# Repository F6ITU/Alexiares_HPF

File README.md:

# Alexiares_HPF
This repository contains the High Pass Filter project of the OpenHPSDR Alexiares frontend

This work is protected by the TAPR Open Hardware Licence https://www.tapr.org/ohl.html

Original work by Graham Haddock, KE9H and Phil Harman, VK6APH.

for more informations, please refer to 

https://wiki.electrolab.fr/Projets:Lab:2017:Peripheriques_Angelia

3D image of the board are stored on this repo

HPF_top.jpg

HPF_bottom.jpg

Bom is available in CSV format

A separate BOM in XLS format is dedicated to filter capacitors

Note that ALL filter caps must be C0G or at least NP0 quality

Schematics, pcb design, modules and libs are in Kicad format

Gerber files are fully compatible with Protel 4.6 format

Board's dimensions are oversized to fit the 5x10 and 10x10cm size of all board of the Hermes project under Kicad:

* Alexandrie (Ἀλεξάνδρεια), Alexiares SPI interface
* Alexi2C ( Ἄλεξις), Alternate Alexiares I2C interface
* Alexiares_lpf (Ἀλεξιάρης) Alexiares low pass filter
* Alexiares_hpf (Ἀλεξιάρης) Alexiares high-pass filter
* Alexiares_Coax_Out (Ἀλεξιάρης ) Alexiares antenna switch boards
* Télémaque (Τηλέμαχος),  SSPA U/V/C°/Refl/FWD sensor for the Mentor board 
* Mentor (Μέντωρ) Micro-controler unit(MCU) and security module controling Telemaque informations
* Ulysse ou Odysseus (Ὀδυσσεύς), medium power reflectometer for the Telemaque/Mentor set
* Themis (Θέμις), low power bidirectionnal reflectometer with pre-distorsion (pure signal) output
* Aiôn (αἰών), 10 MHz low drift, low phase noise clock (general purpose)
* Hébé (Ἥβη), EER control system for high efficiency power amp

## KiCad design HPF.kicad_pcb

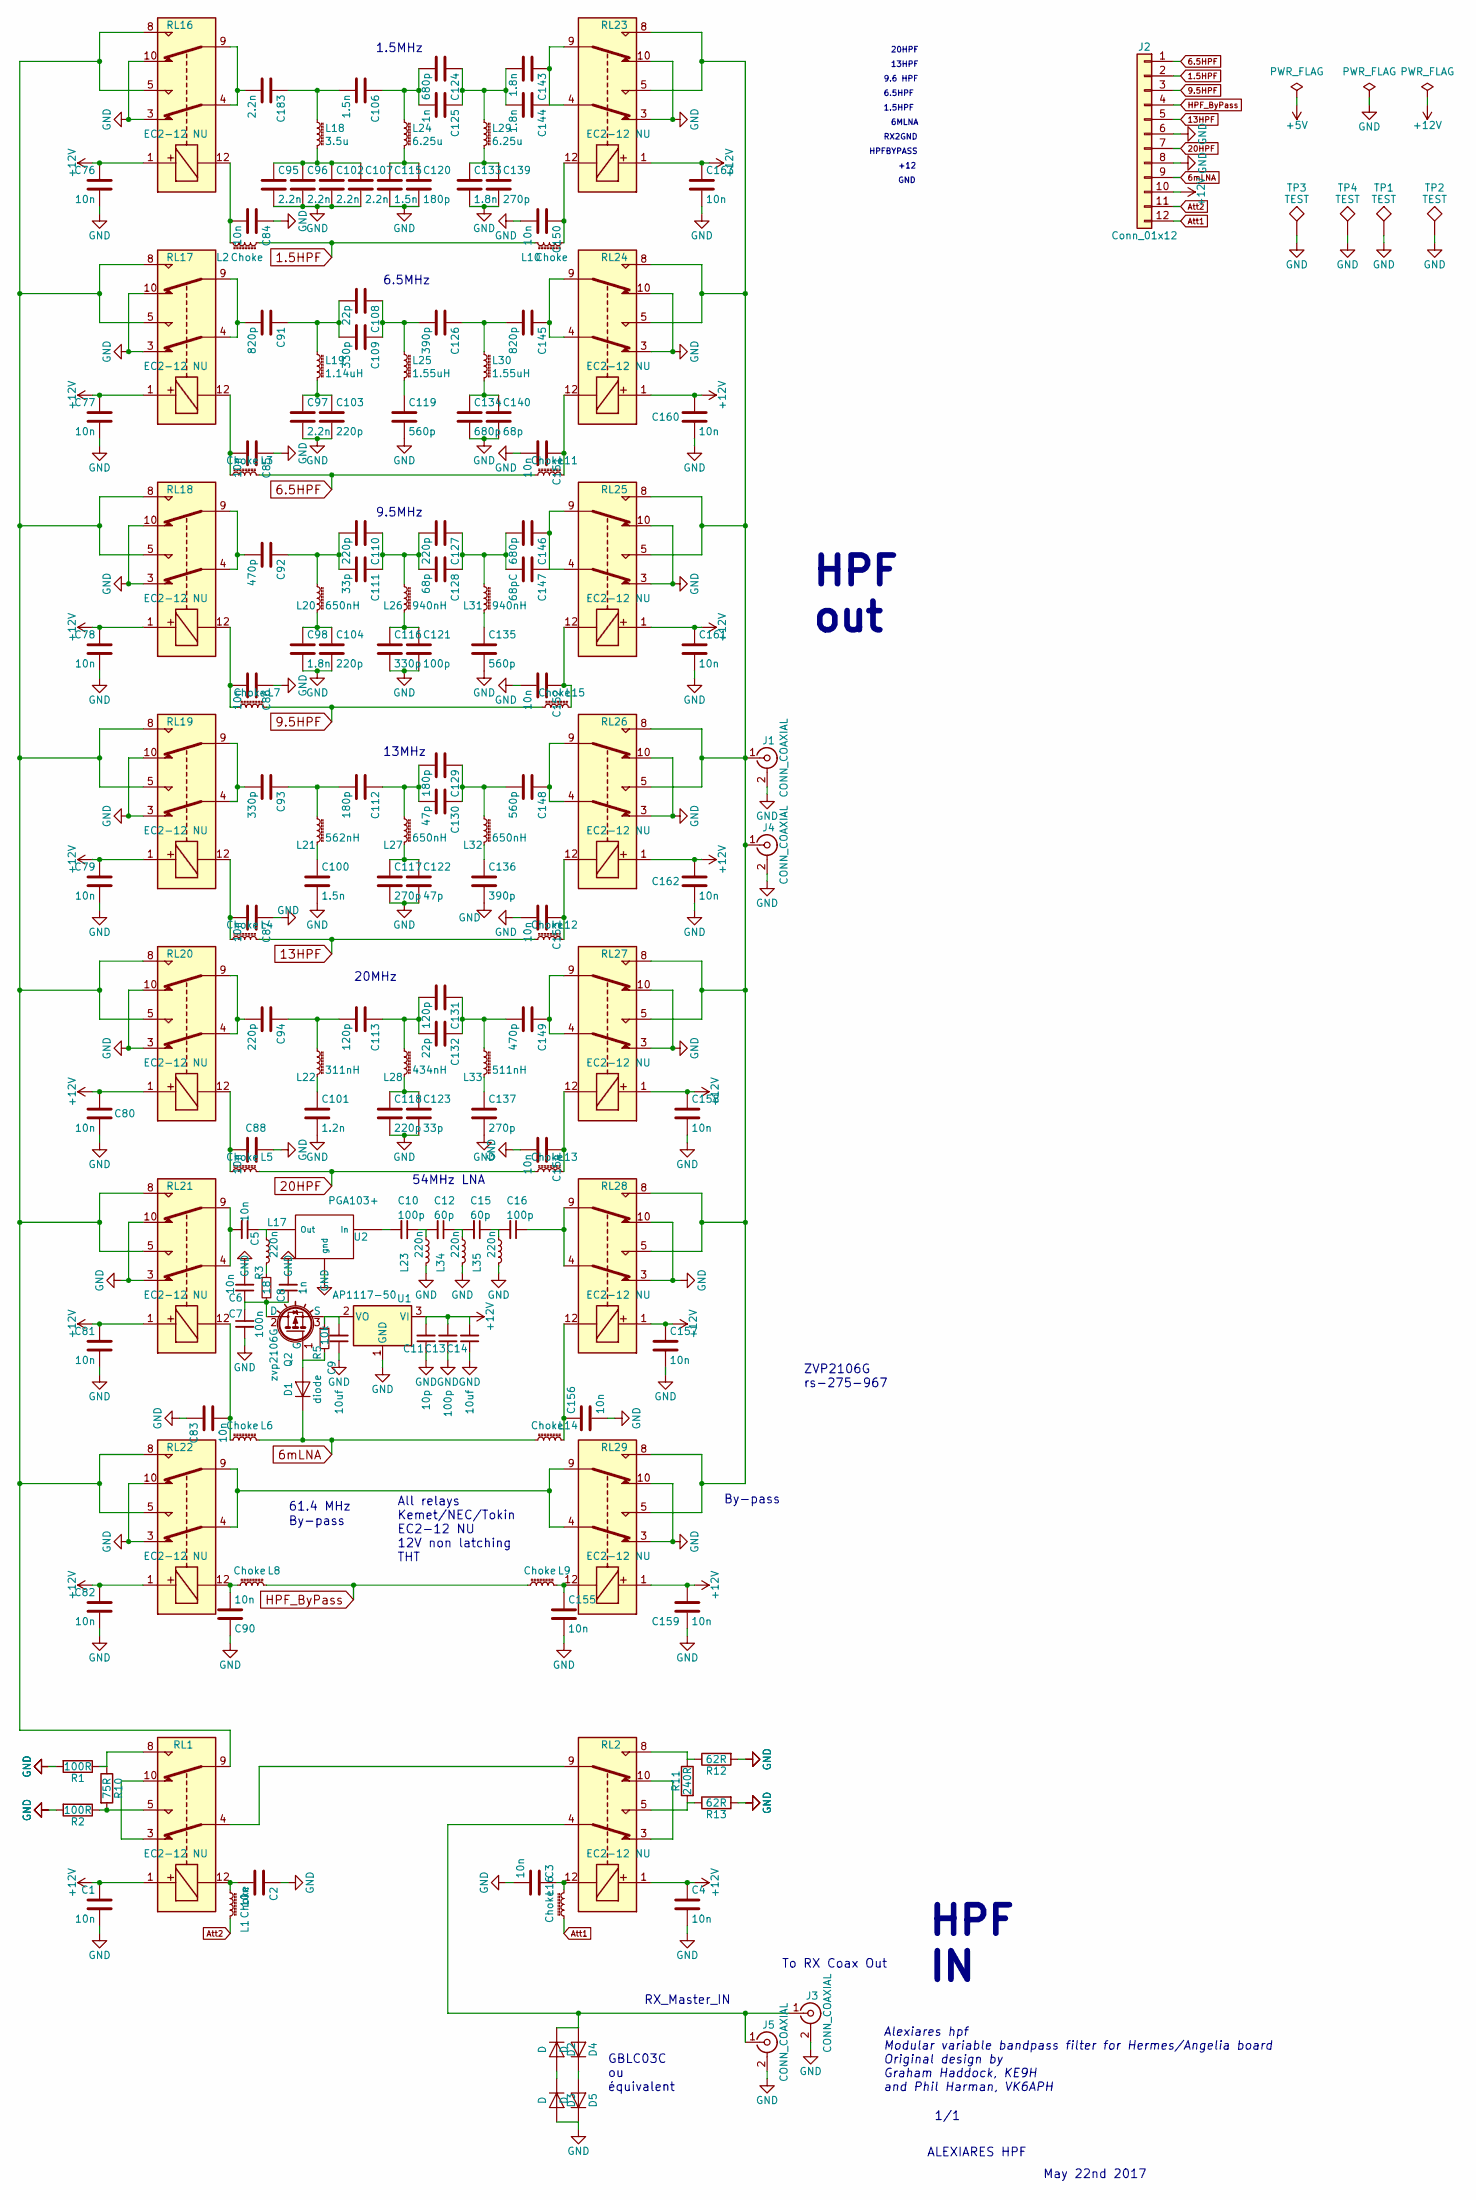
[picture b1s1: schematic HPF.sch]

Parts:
C1, C2, C3, C4, C5, C6, C76, C77, C78, C79, C80, C81, C82, C83, C84, C85, C86, C87, C88, C90, C150, C151, C152, C153, C154, C155, C156, C157, C158, C159, C160, C161, C162, C163: 10n; C_0805_HandSoldering
C7: 100n; C_0805_HandSoldering
C8: 1n; C_0805_HandSoldering
C9, C14: 10uf; CP_Tantalum_Case-B_EIA-3528-21_Hand
C10, C13, C16: 100p; C_0805_HandSoldering
C11: 10p; C_0805_HandSoldering
C12, C15: 60p; C_0805_HandSoldering
C91, C145: 820p; C_1206_HandSoldering
C92, C149: 470p; C_1206_HandSoldering
C93, C109, C116: 330p; C_1206_HandSoldering
C94, C103, C104, C110, C118, C127: 220p; C_1206_HandSoldering
C95, C96, C97, C102, C107, C183: 2.2n; C_1206_HandSoldering
C98, C133, C143, C144: 1.8n; C_1206_HandSoldering
C100, C106, C115: 1.5n; C_1206_HandSoldering
C101: 1.2n; C_1206_HandSoldering
C108, C132: 22p; C_1206_HandSoldering
C111, C123: 33p; C_1206_HandSoldering
C112, C120, C129: 180p; C_1206_HandSoldering
C113, C131: 120p; C_1206_HandSoldering
C117, C137, C139: 270p; C_1206_HandSoldering
C119, C135, C148: 560p; C_1206_HandSoldering
C121: 100p; C_1206_HandSoldering
C122, C130: 47p; C_1206_HandSoldering
C124, C134, C146: 680p; C_1206_HandSoldering
C125: 1n; C_1206_HandSoldering
C126, C136: 390p; C_1206_HandSoldering
C128, C140: 68p; C_1206_HandSoldering
C147: 68pC; C_1206_HandSoldering
D1: diode; D_1206
D2, D3, D4, D5: D; D_0805
J1, J3: CONN_COAXIAL; SMA_THT_Jack_Straight
J2: Conn_01x12; IDC_Header_Straight_12pins
J4, J5: CONN_COAXIAL; SMA_EDGE_NRW
L1, L2, L3, L4, L5, L6, L7, L8, L9, L10, L11, L12, L13, L14, L15, L16: Choke; L_0805_HandSoldering
L17, L23, L34, L35: 220n; L_0805_HandSoldering
L18: 3.5u; T50_V_THT
L19: 1.14uH; T50_V_THT
L20, L27, L32: 650nH; T50_V_THT
L21: 562nH; T50_V_THT
L22: 311nH; T50_V_THT
L24, L29: 6.25u; T50_V_THT
L25, L30: 1.55uH; T50_V_THT
L26, L31: 940nH; T50_V_THT
L28: 434nH; T50_V_THT
L33: 511nH; T50_V_THT
Q2: zvp2106G; SOT-223-3Lead_TabPin2
R1, R2: 100R; R_0805_HandSoldering
R3: 18; R_0805_HandSoldering
R5: 10k; R_0805_HandSoldering
R10: 75R; R_0805_HandSoldering
R11: 240R; R_0805_HandSoldering
R12, R13: 62R; R_0805_HandSoldering
RL1, RL2, RL16, RL17, RL18, RL19, RL20, RL21, RL22, RL23, RL24, RL25, RL26, RL27, RL28, RL29: EC2-12 NU; Relay_DPDT_NEC_EC2
TP1, TP2, TP3, TP4: TEST; MountingHole_3.5mm_Pad
U1: AP1117-50; SOT-223-3_TabPin2
U2: PGA103+; SOT-89-3_Handsoldering

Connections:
1.5HPF: J2.2, L2.1, L10.2
6.5HPF: J2.1, L3.2, L11.1
6mLNA: D1.1 (K), J2.9, L6.2, L14.1
9.5HPF: J2.3, L7.2, L15.1
13HPF: J2.5, L4.2, L12.1
20HPF: J2.7, L5.2, L13.1
+12V: C1.1, C4.1, C11.2, C13.2, C14.2, C76.1, C77.1, C78.1, C79.1, C80.1, C81.1, C82.1, C157.1, C158.1, C159.1, C160.1, C161.1, C162.1, C163.1, J2.10, RL1.1, RL2.1, RL16.1, RL17.1, RL18.1, RL19.1, RL20.1, RL21.1, RL22.1, RL23.1, RL24.1, RL25.1, RL26.1, RL27.1, RL28.1, RL29.1, U1.3 (VI)
Att1: J2.12, L16.1
Att2: J2.11, L1.2
GND: C1.2, C2.1, C3.2, C4.2, C6.2, C7.2, C8.2, C9.1, C11.1, C13.1, C14.1, C76.2, C77.2, C78.2, C79.2, C80.2, C81.2, C82.2, C83.1, C84.1, C85.1, C86.1, C87.1, C88.1, C90.1, C95.2, C96.2, C97.2, C98.2, C100.2, C101.2, C102.2, C103.2, C104.2, C107.2, C115.2, C116.2, C117.2, C118.2, C119.2, C120.2, C121.2, C122.2, C123.2, C133.2, C134.2, C135.2, C136.2, C137.2, C139.2, C140.2, C150.2, C151.2, C152.2, C153.2, C154.2, C155.2, C156.2, C157.2, C158.2, C159.2, C160.2, C161.2, C162.2, C163.2, D3.2 (A), D5.1 (K), J1.2 (Ext), J2.6, J2.8, J3.2 (Ext), J4.2 (Ext), J5.2 (Ext), L23.2, L34.2, L35.2, R1.2, R2.2, R12.2, R13.2, RL16.3, RL16.10, RL17.3, RL17.10, RL18.3, RL18.10, RL19.3, RL19.10, RL20.3, RL20.10, RL21.3, RL21.10, RL22.3, RL22.10, RL23.3, RL23.10, RL24.3, RL24.10, RL25.3, RL25.10, RL26.3, RL26.10, RL27.3, RL27.10, RL28.3, RL28.10, RL29.3, RL29.10, TP1.1, TP2.1, TP3.1, TP4.1, U1.1 (GND), U2.2 (gnd)
HPF_ByPass: J2.4, L8.2, L9.1
unnamed: C2.2, L1.1, RL1.12
unnamed: C3.1, L16.2, RL2.12
unnamed: C5.1, L17.1, U2.3 (Out)
unnamed: C5.2, RL21.4, RL21.9
unnamed: C6.1, C7.1, C8.1, Q2.2 (D), R3.2
unnamed: C9.2, Q2.3 (S), R5.1, U1.2 (VO)
unnamed: C10.1, C12.2, L23.1
unnamed: C10.2, U2.1 (In)
unnamed: C12.1, C15.2, L34.1
unnamed: C15.1, C16.2, L35.1
unnamed: C16.1, RL28.4, RL28.9
unnamed: C83.2, L6.1, RL21.12
unnamed: C84.2, L2.2, RL16.12
unnamed: C85.2, L3.1, RL17.12
unnamed: C86.2, L7.1, RL18.12
unnamed: C87.2, L4.1, RL19.12
unnamed: C88.2, L5.1, RL20.12
unnamed: C90.2, L8.1, RL22.12
unnamed: C91.2, RL17.4, RL17.9
unnamed: C92.2, RL18.4, RL18.9
unnamed: C93.2, RL19.4, RL19.9
unnamed: C94.2, RL20.4, RL20.9
unnamed: C100.1, L21.2
unnamed: C101.1, L22.2
unnamed: C95.1, C96.1, C102.1, C107.1, L18.2
unnamed: C97.1, C103.1, L19.2
unnamed: C98.1, C104.1, L20.2
unnamed: C106.1, C124.2, C125.2, L24.1
unnamed: C106.2, C183.1, L18.1
unnamed: C108.1, C109.1, C126.2, L25.1
unnamed: C91.1, C108.2, C109.2, L19.1
unnamed: C110.1, C111.1, C127.2, C128.2, L26.1
unnamed: C92.1, C110.2, C111.2, L20.1
unnamed: C112.1, C129.2, C130.2, L27.1
unnamed: C93.1, C112.2, L21.1
unnamed: C113.1, C131.2, C132.2, L28.1
unnamed: C94.1, C113.2, L22.1
unnamed: C115.1, C120.1, L24.2
unnamed: C116.1, C121.1, L26.2
unnamed: C117.1, C122.1, L27.2
unnamed: C118.1, C123.1, L28.2
unnamed: C119.1, L25.2
unnamed: C124.1, C125.1, C143.2, C144.2, L29.1
unnamed: C126.1, C145.2, L30.1
unnamed: C127.1, C128.1, C146.2, C147.2, L31.1
unnamed: C129.1, C130.1, C148.2, L32.1
unnamed: C131.1, C132.1, C149.2, L33.1
unnamed: C133.1, C139.1, L29.2
unnamed: C134.1, C140.1, L30.2
unnamed: C135.1, L31.2
unnamed: C136.1, L32.2
unnamed: C137.1, L33.2
unnamed: C143.1, C144.1, RL23.4, RL23.9
unnamed: C145.1, RL24.4, RL24.9
unnamed: C146.1, C147.1, RL25.4, RL25.9
unnamed: C148.1, RL26.4, RL26.9
unnamed: C149.1, RL27.4, RL27.9
unnamed: C150.1, L10.1, RL23.12
unnamed: C151.1, L11.2, RL24.12
unnamed: C152.1, L15.2, RL25.12
unnamed: C153.1, L12.2, RL26.12
unnamed: C154.1, L13.2, RL27.12
unnamed: C155.1, L9.2, RL29.12
unnamed: C156.1, L14.2, RL28.12
unnamed: C183.2, RL16.4, RL16.9
unnamed: D1.2 (A), Q2.1 (G), R5.2
unnamed: D2.1 (K), D4.2 (A), J3.1 (In), J5.1 (In), RL2.4
unnamed: D2.2 (A), D3.1 (K)
unnamed: D4.1 (K), D5.2 (A)
unnamed: J1.1 (In), J4.1 (In), RL23.5, RL23.8, RL24.5, RL24.8, RL25.5, RL25.8, RL26.5, RL26.8, RL27.5, RL27.8, RL28.5, RL28.8, RL29.5, RL29.8
unnamed: L17.2, R3.1
unnamed: R1.1, R10.1, RL1.8
unnamed: R2.1, R10.2, RL1.5
unnamed: R11.1, R12.1, RL2.8
unnamed: R11.2, R13.1, RL2.5
unnamed: RL1.4, RL2.9
unnamed: RL1.9, RL16.5, RL16.8, RL17.5, RL17.8, RL18.5, RL18.8, RL19.5, RL19.8, RL20.5, RL20.8, RL21.5, RL21.8, RL22.5, RL22.8
unnamed: RL1.3, RL1.10
unnamed: RL2.3, RL2.10
unnamed: RL22.4, RL22.9, RL29.4, RL29.9

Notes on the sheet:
Alexiares hpf Modular variable bandpass filter for Hermes/Angelia board Original design by Graham Haddock, KE9H and Phil Harman, VK6APH
1/1
ALEXIARES HPF
May 22nd 2017
HPF IN
HPF out
61.4 MHz
All relays Kemet/NEC/Tokin EC2-12 NU 12V non latching THT
By-pass
54MHz LNA
20MHz
13MHz
9.5MHz
6.5MHz
1.5MHz
20HPF
13HPF
9.6 HPF
6.5HPF
1.5HPF
6MLNA
RX2GND
HPFBYPASS
+12
GND
To RX Coax Out
GBLC03C ou équivalent
ZVP2106G rs-275-967
RX_Master_IN

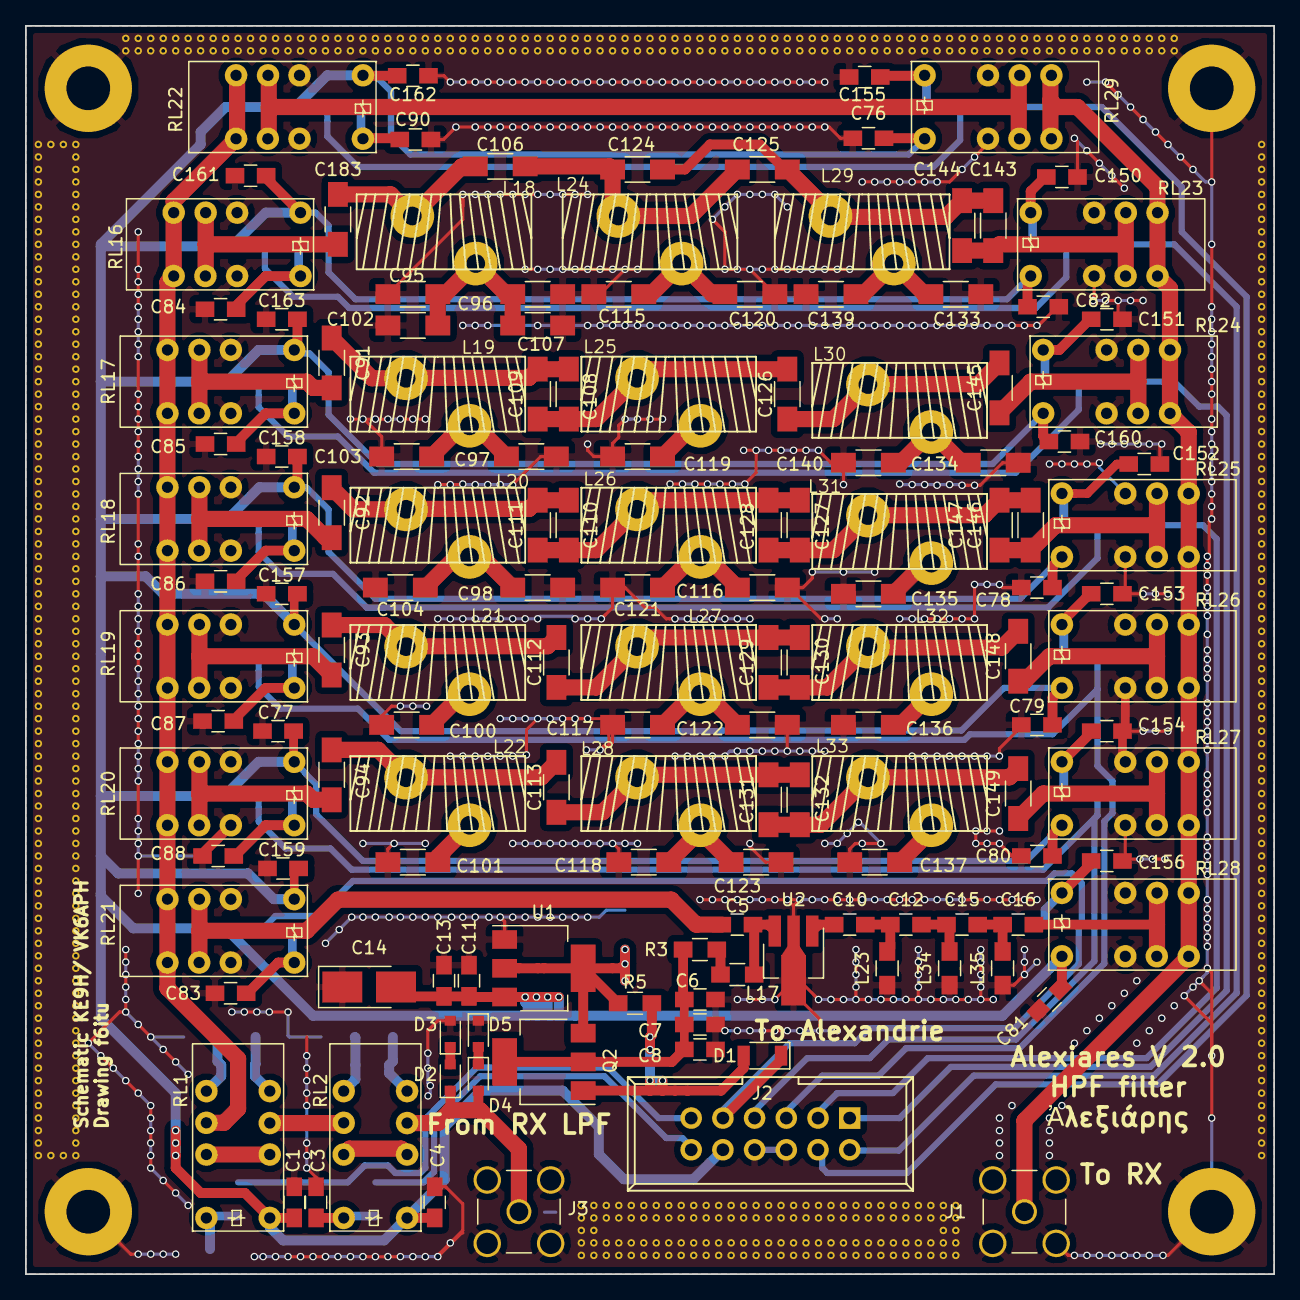
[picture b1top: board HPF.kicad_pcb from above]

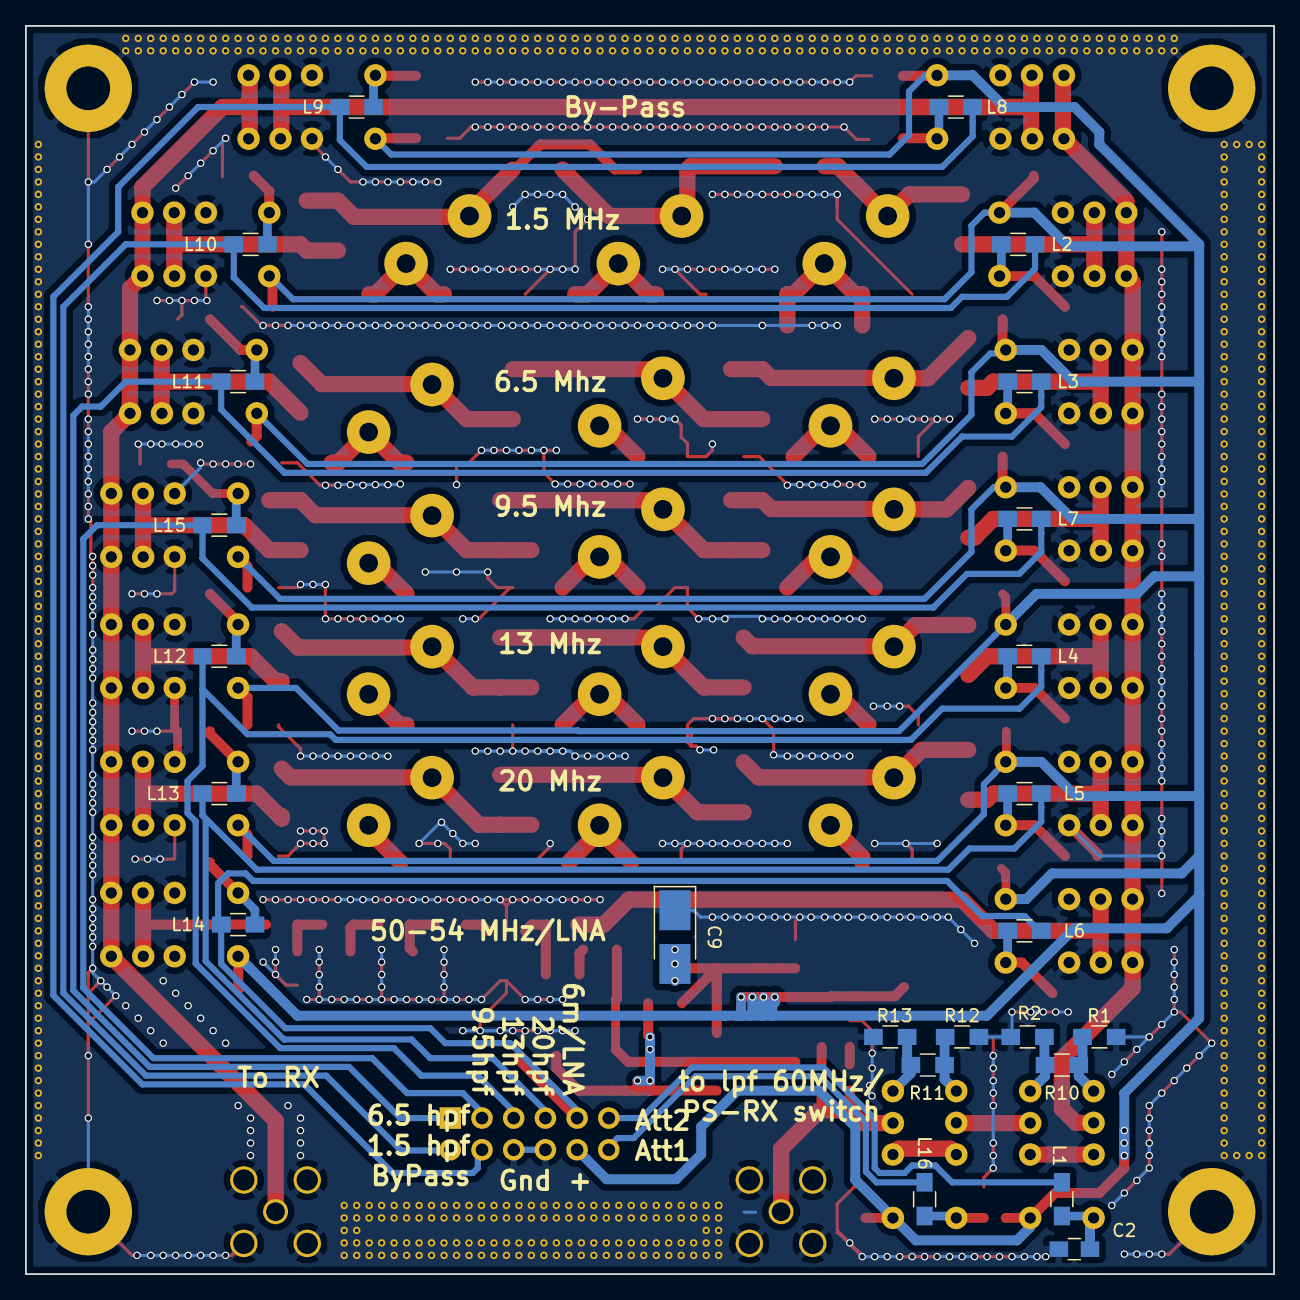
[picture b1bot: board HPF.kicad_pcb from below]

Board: 4 copper layers, 100.0 x 100.0 mm, 172 parts (24 on the bottom side), 91 nets.

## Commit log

2017-06-12 hpf V1.0, compatible w OpenHPSDR Ver24
2017-11-01 minor changes, still in dev.
2017-11-01 modif du readme
2017-11-09 firt routing, 6m LPF discarted
2017-11-12 silkmask cleanup and comments added
2017-11-14 New LNA, silkmask modified
2017-11-27 new ferrite footprint/module
2017-12-12 edge SMA added, main connector shifted
2017-12-16 changed sma footprint, gerber done
2018-01-06 new stitching, new gerber
2018-01-09 BOM added, new Gerber
2018-01-10 silkmask mods,, gnd stitching cleaning, gerber added
2018-01-13 minor changes, new gerber
2018-01-13 test
2018-01-13 totot
2018-01-13 cleaning bak
2018-01-14 Bad MosFET footprint corrected, new gerber
2018-01-22 new gerber
2018-02-12 minor stiching error gone, new inductance spreadsheet
2018-02-12 some stiching error fixed
2019-03-15 upgrate to Kicad 5.0n, new up to date Gerber
